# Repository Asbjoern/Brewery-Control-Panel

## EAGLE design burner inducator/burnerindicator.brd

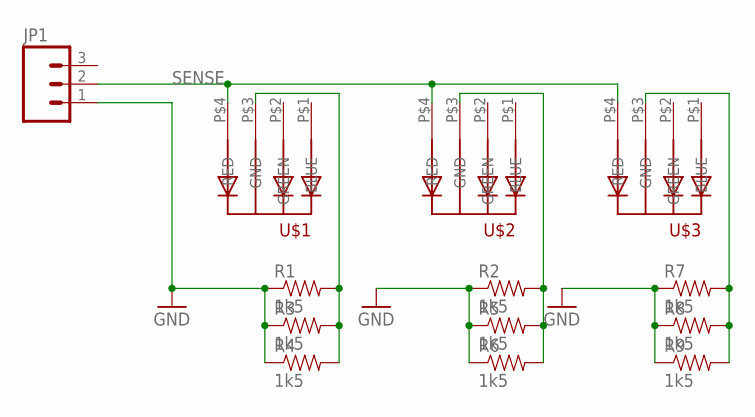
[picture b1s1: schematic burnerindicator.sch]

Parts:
JP1: M03POLAR_LOCK; MOLEX-1X3_LOCK
R1, R2, R3, R4, R5, R6, R7, R8, R9: 1k5; 0603-RES
U$1, U$2, U$3: 5MMRGBLED; LED5MMRGB

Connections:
GND: JP1.1, R1.1, R2.1, R3.1, R4.1, R5.1, R6.1, R7.1, R8.1, R9.1
unnamed: R1.2, R3.2, R4.2, U$1.P$3 (GND)
unnamed: R2.2, R5.2, R6.2, U$2.P$3 (GND)
unnamed: R7.2, R8.2, R9.2, U$3.P$3 (GND)
SENSE: JP1.2, U$1.P$4 (RED), U$2.P$4 (RED), U$3.P$4 (RED)

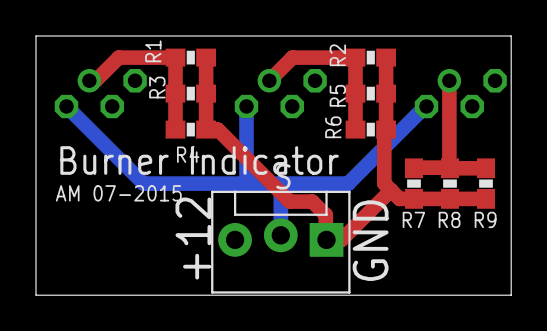
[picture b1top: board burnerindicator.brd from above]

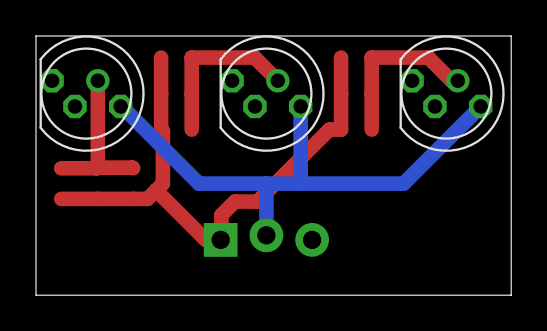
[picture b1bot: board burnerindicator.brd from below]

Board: 2 copper layers, 26.4 x 14.4 mm, 13 parts (3 on the bottom side), 5 nets.

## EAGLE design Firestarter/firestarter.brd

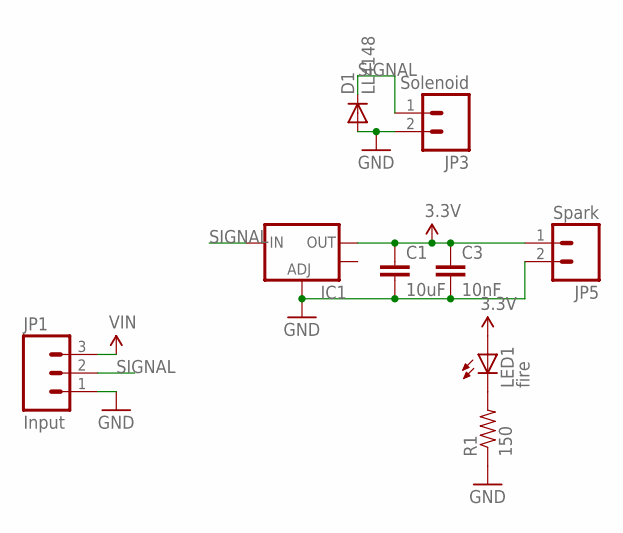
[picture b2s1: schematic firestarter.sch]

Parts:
C1: 10uF; 0603-CAP
C3: 10nF; 0603-CAP
D1: LL4148; MLL34
IC1: V_REG_LM1117SOT223; SOT223
JP1: Input; MOLEX-1X3_LOCK
JP3: Solenoid; MOLEX-1X2_LOCK
JP5: Spark; MOLEX-1X2_LOCK
LED1: fire; LED-0603
R1: 150; 0603-RES

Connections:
3.3V: C1.1, C3.1, IC1.2 (OUT), JP5.1, LED1.A
GND: C1.2, C3.2, D1.A, IC1.1 (ADJ), JP1.1, JP3.2, JP5.2, R1.1
unnamed: LED1.C, R1.2
SIGNAL: D1.C, IC1.3 (IN), JP1.2, JP3.1
VIN: JP1.3

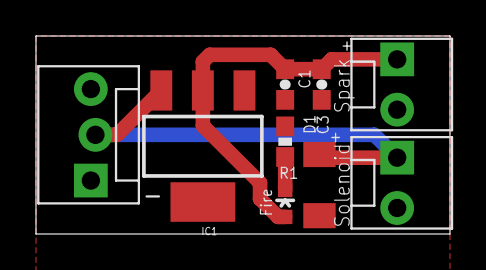
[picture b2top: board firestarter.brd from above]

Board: 2 copper layers, 23.0 x 11.0 mm, 9 parts (0 on the bottom side), 4 nets.

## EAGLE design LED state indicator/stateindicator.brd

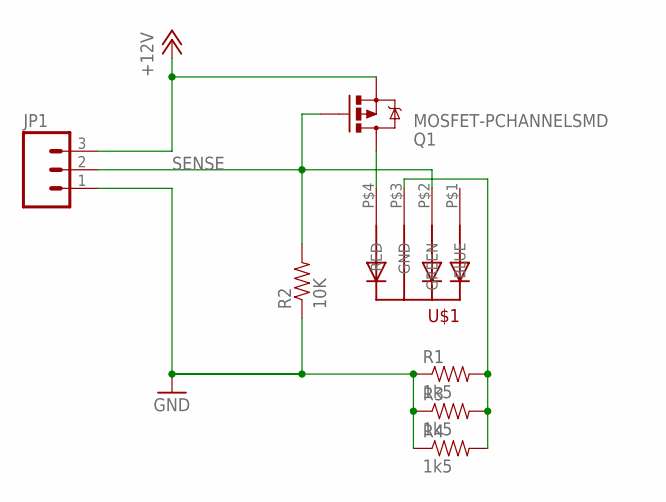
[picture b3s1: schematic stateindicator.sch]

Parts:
JP1: M03POLAR_LOCK; MOLEX-1X3_LOCK
Q1: MOSFET-PCHANNELSMD; SOT23-3
R1, R3, R4: 1k5; 0603-RES
R2: 10K; 0603-RES
U$1: 5MMRGBLED; LED5MMRGB

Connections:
+12V: JP1.3, Q1.2 (S)
GND: JP1.1, R1.1, R2.1, R3.1, R4.1
unnamed: R1.2, R3.2, R4.2, U$1.P$3 (GND)
unnamed: Q1.3 (D), U$1.P$4 (RED)
SENSE: JP1.2, Q1.1 (G), R2.2, U$1.P$2 (GREEN)

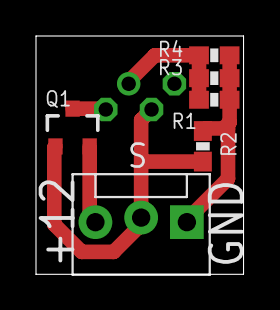
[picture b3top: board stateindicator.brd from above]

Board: 2 copper layers, 11.5 x 13.2 mm, 7 parts (1 on the bottom side), 5 nets.

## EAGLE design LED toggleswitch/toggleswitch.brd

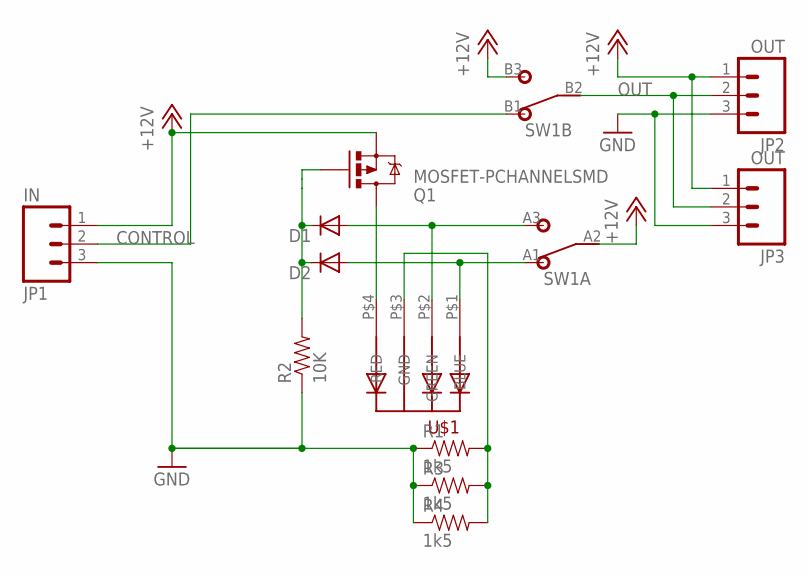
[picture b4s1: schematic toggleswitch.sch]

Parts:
D1, D2: DIODE-MINIMELF; MINIMELF
JP1: IN; MOLEX-1X3_LOCK
JP2, JP3: OUT; MOLEX-1X3_LOCK
Q1: MOSFET-PCHANNELSMD; SOT23-3
R1, R3, R4: 1k5; 0603-RES
R2: 10K; 0603-RES
SW1: DPDT
U$1: 5MMRGBLED; LED5MMRGB

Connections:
+12V: JP1.1, JP2.1, JP3.1, Q1.2 (S), SW1.A2 (2), SW1.B3 (3)
CONTROL: JP1.2, SW1.B1 (1)
GND: JP1.3, JP2.3, JP3.3, R1.1, R2.1, R3.1, R4.1
unnamed: R1.2, R3.2, R4.2, U$1.P$3 (GND)
unnamed: D1.C, D2.C, Q1.1 (G), R2.2
unnamed: D1.A, SW1.A3 (3), U$1.P$2 (GREEN)
unnamed: D2.A, SW1.A1 (1), U$1.P$1 (BLUE)
unnamed: Q1.3 (D), U$1.P$4 (RED)
OUT: JP2.2, JP3.2, SW1.B2 (2)

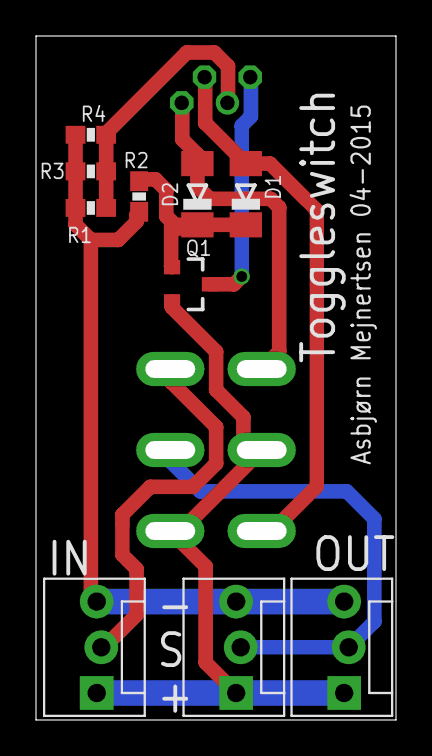
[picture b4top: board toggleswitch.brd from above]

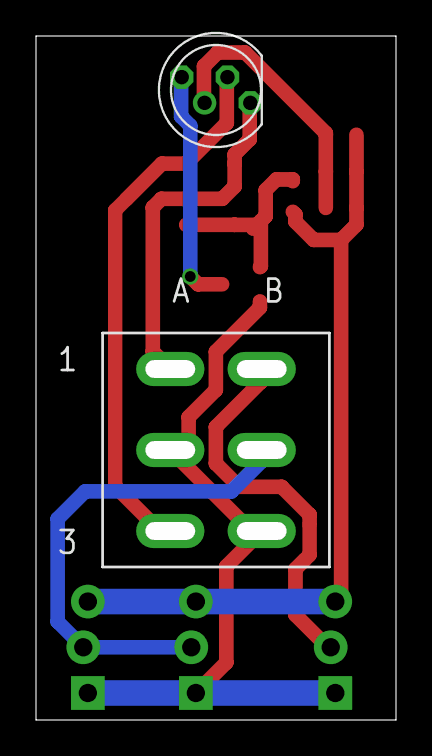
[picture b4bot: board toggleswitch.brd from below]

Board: 2 copper layers, 19.0 x 37.0 mm, 12 parts (2 on the bottom side), 9 nets.

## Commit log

2015-05-08 Brewery control panel for Brewtroller HERMES setup
2015-05-22 Added connector panel and added room for LED collar
2015-07-23 Reworked PCB
2016-02-23 Minor updates

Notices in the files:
parts and their libraries:
SparkFun-Capacitors: Licensing: CC v3.0 Share-Alike You are welcome to use this library for commercial purposes.
